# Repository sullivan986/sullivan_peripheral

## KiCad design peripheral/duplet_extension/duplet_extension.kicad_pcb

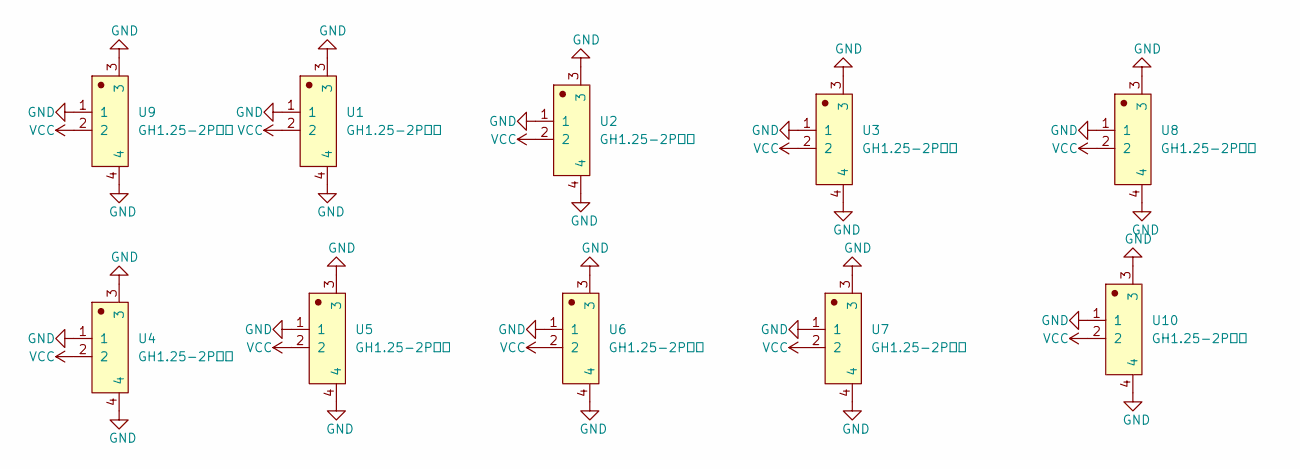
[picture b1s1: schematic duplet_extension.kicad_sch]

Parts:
U1, U2, U3, U4, U5, U6, U7, U8, U9, U10: GH1.25-2P卧贴; JST_GH_SM02B-GHS-TB_1x02-1MP_P1.25mm_Horizontal

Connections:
GND: U1.1, U1.3, U1.4, U2.1, U2.3, U2.4, U3.1, U3.3, U3.4, U4.1, U4.3, U4.4, U5.1, U5.3, U5.4, U6.1, U6.3, U6.4, U7.1, U7.3, U7.4, U8.1, U8.3, U8.4, U9.1, U9.3, U9.4, U10.1, U10.3, U10.4
VCC: U1.2, U2.2, U3.2, U4.2, U5.2, U6.2, U7.2, U8.2, U9.2, U10.2

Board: 2 copper layers, 10 parts (0 on the bottom side), 2 nets, no tracks yet.

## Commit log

2024-01-12 add duplet_extension
